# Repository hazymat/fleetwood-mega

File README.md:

# fleetwood-mega
Eagle files for Version 2 of Fleetwood hardware.

Hi reader! The PCB in this project is not ready for production. Parts have not been finalised, traces not yet routed. It's a work in progress.

Latest YouTube project update here: https://www.youtube.com/watch?v=HE-3FGcSKfI
YouTube channel generally full of my MQTT ramblings here: https://www.youtube.com/user/hazymat

Do take a look at the photo of Fleetwood's first prototype installed in the home, included in the repo.

- This project is not ready for production
- The board is based on Freetronics EtherMegaR3 (https://github.com/freetronics/EtherMega)
- Spec as per EtherMega with following changes
 - **Inclusion of 7 LED tactile switches, a click rotary encoder, and OLED display, for controlling home automation hub by MQTT**
 - Change form factor to better fit a double wall socket back box - dry lining box and metal back box
 - Removal of SD card to save space
 - Removal of USB to serial to save space (use external FTDI or TFTP upload of sketch to bootloader)
 - Built-in support for either DIY PoE or 802.3af PoE - as per original EtherMega
 - Ethernet jack moved away from side of board to allow more space for cable / plug insertion in wall box

# LICENCE
This work is licensed under the
Creative Commons Attribution-Share Alike License.  
To view a copy of this license, visit

  http://creativecommons.org/licenses/by-sa/3.0/  
  http://creativecommons.org/licenses/by-sa/3.0/legalcode

or send a letter to

  Creative Commons  
  171 Second Street, Suite 300  
  San Francisco  
  California, 94105  
  USA

The "license" folder within this repository also contains copies of the
licences referenced above.

# CREDITS
The EtherMega was designed by Marc Alexander (marc@freetronics.com) and
Jonathan Oxer (jon@freetronics.com) based on previous work by the Arduino
team (www.arduino.cc/playground/Main/People) which includes:

 * Massimo Banzi
 * David Cuartielles
 * Tom Igoe
 * Gianluca Martino
 * David A. Mellis

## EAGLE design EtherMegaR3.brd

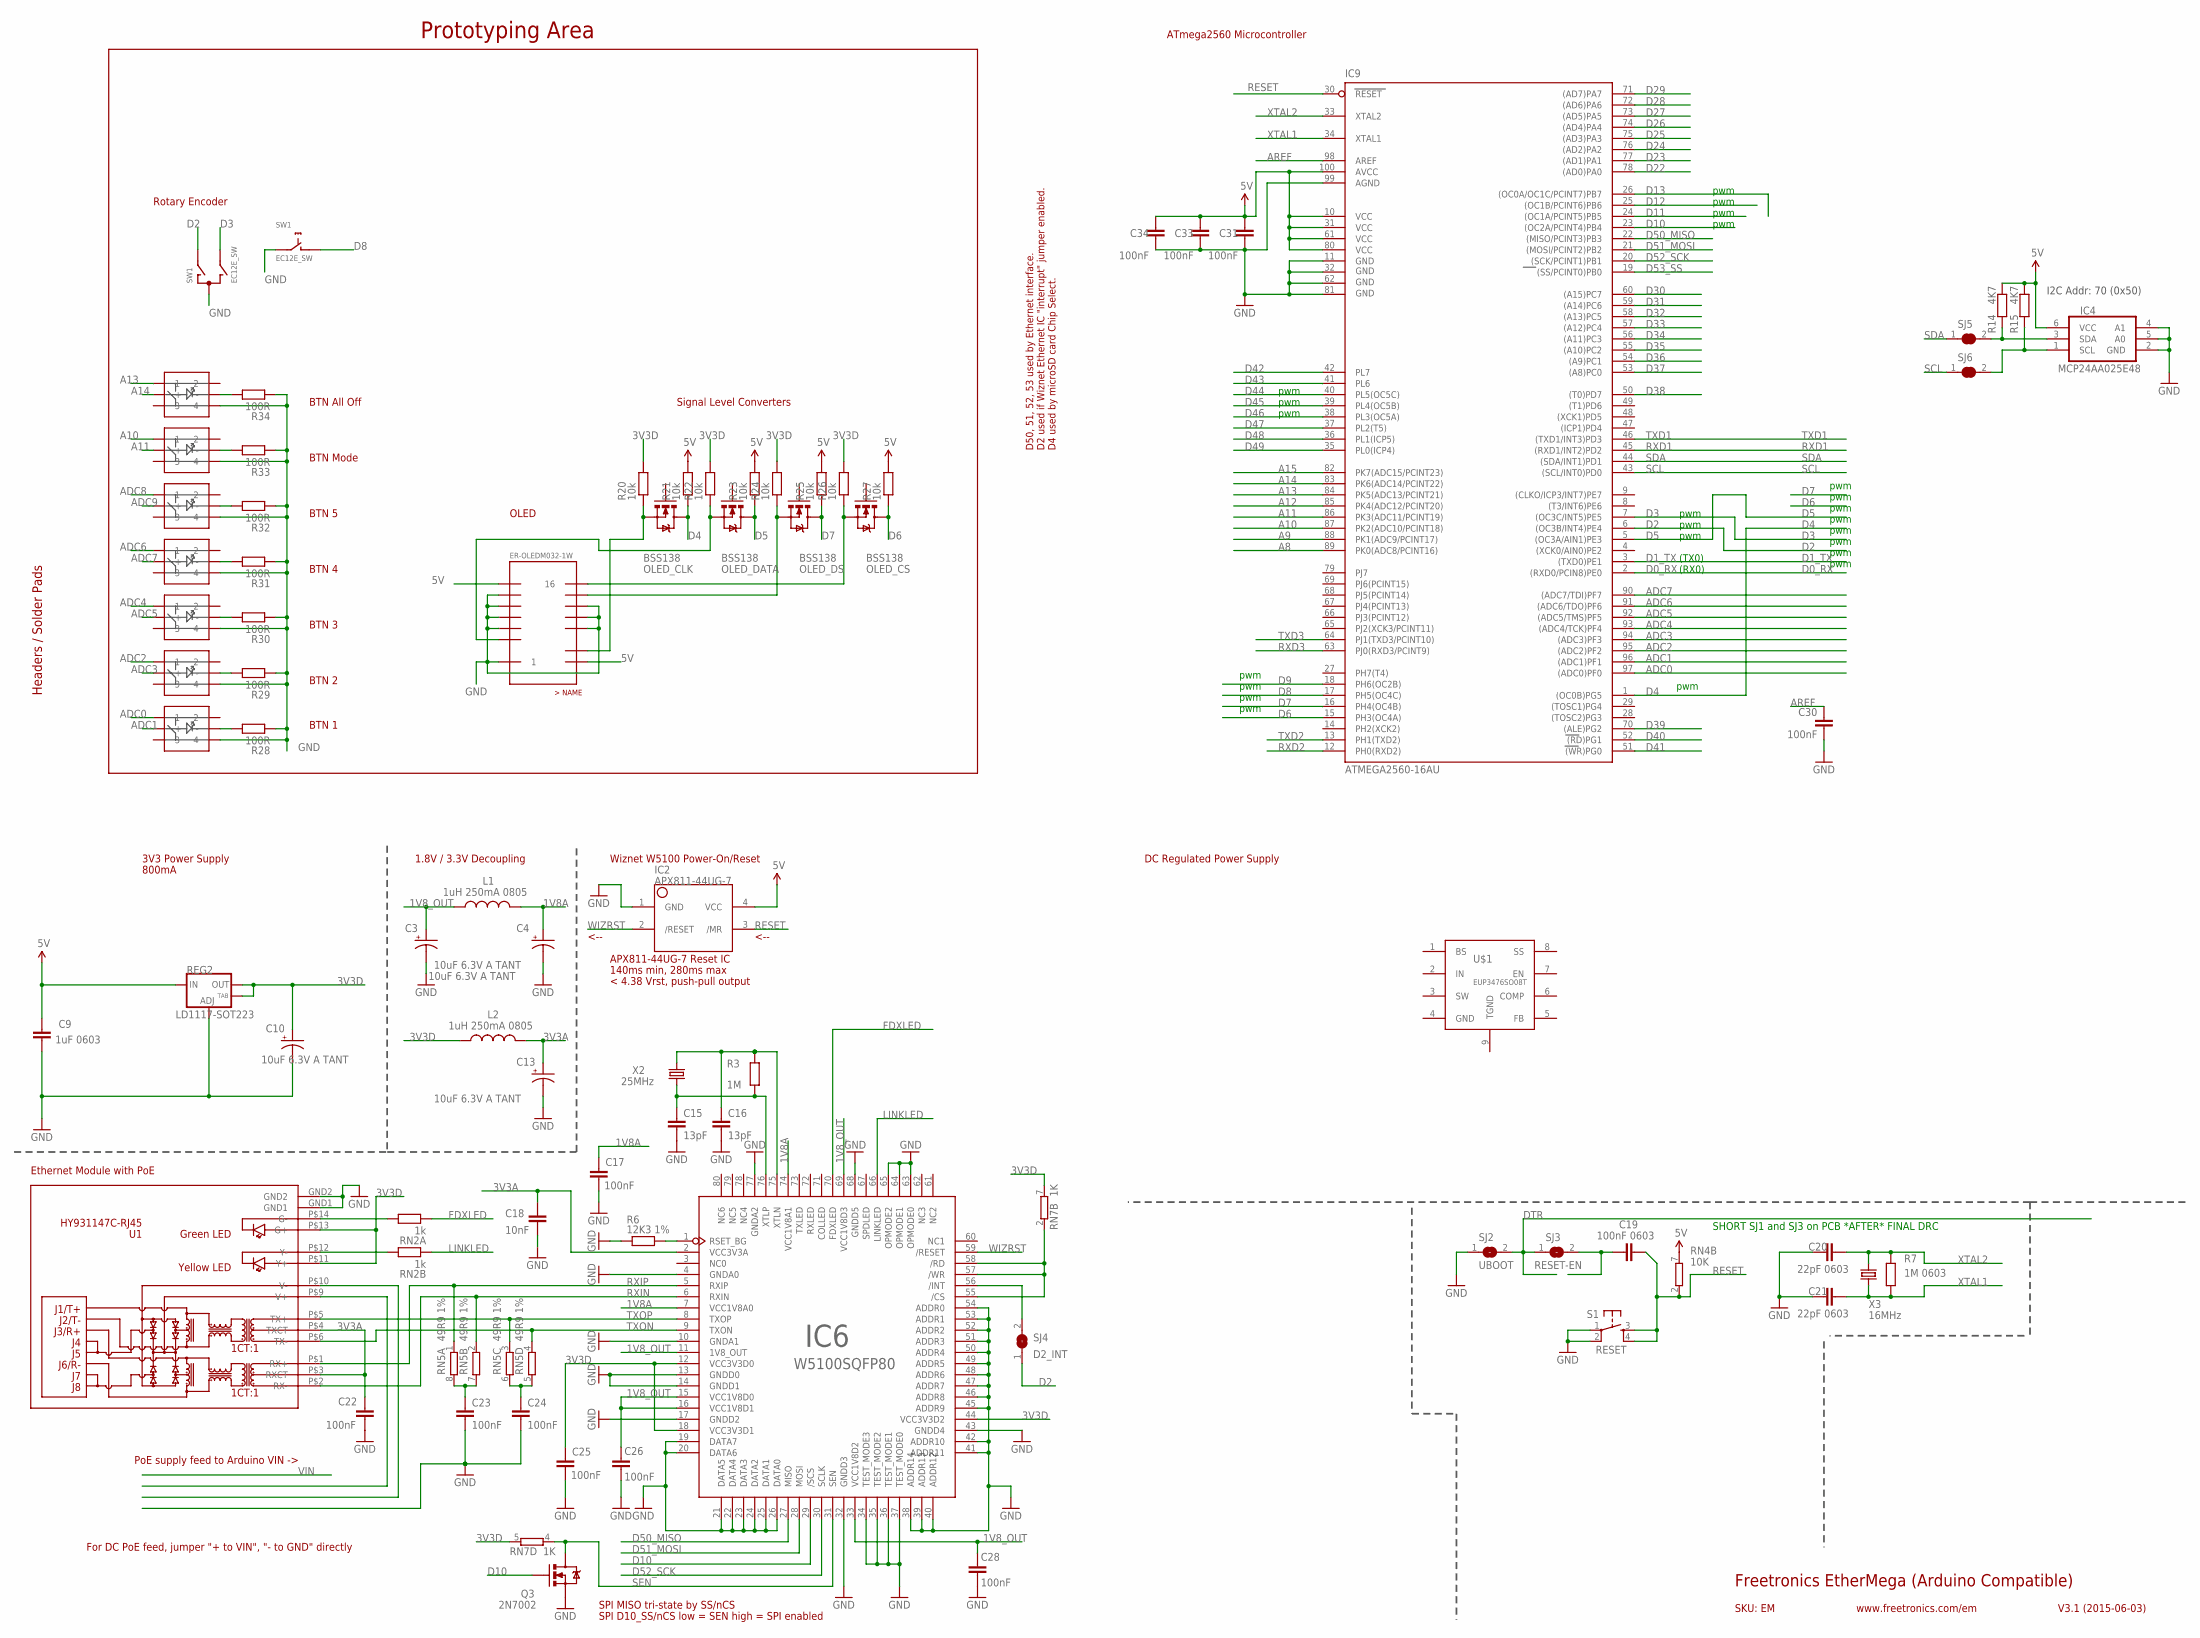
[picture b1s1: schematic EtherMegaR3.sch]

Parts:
BTN_FAVE1, BTN_FAVE2, BTN_FAVE3, BTN_FAVE4, BTN_FAVE5: PB614
BTN_MODE: PB614
BTN_OFF: PB614
C3, C4, C10, C13: 10uF 6.3V A TANT; EIA3216
C9: 1uF 0603; 0603
C15, C16: 13pF; 0603
C17, C22, C23, C24, C25, C26, C28, C30, C31, C33, C34: 100nF; 0603
C18: 10nF; 0603
C19: 100nF 0603; 0603
C20, C21: 22pF 0603; 0603
IC2: APX811-44UG-7; SOT143-R
IC4: MCP24AA025E48; SOT23-6
IC6: W5100SQFP80; SQFP80
IC9: ATMEGA2560-16AU; TQFP100
L1, L2: 1uH 250mA 0805; L2012C
OLED: ER-OLED-M032-1W
OLED_CLK: BSS138; SOT23-3
OLED_CS: BSS138; SOT23-3
OLED_DATA: BSS138; SOT23-3
OLED_DS: BSS138; SOT23-3
Q3: 2N7002; SOT23-3
R3: 1M; 0603
R6: 12K3 1%; 0603
R7: 1M 0603; 0603
R14, R15: 4K7; 0603
R20, R21, R22, R23, R24, R25, R26, R27: 10k; 0603
R28, R29, R30, R31, R32, R33, R34: 100R; 0603
REG2: LD1117-SOT223; SOT223
RN2A, RN2B: 1k; 0603
RN4: 10K; CAY16
RN5: 49R9 1%; CAY16
RN7: 1K; CAY16
S1: RESET; TACTILE_SWITCH_SMD
SJ2: UBOOT; SJ
SJ3: RESET-EN; SJ
SJ4: D2_INT; SJ
SJ5, SJ6: SJCN; SJC
SW1: EC12E_SW; ALPS_EC12E_SW
U1: HY931147C-RJ45; HY931147C
U$1: EUP3476SO08T; SO08T
X2: 25MHz; HC49U-V
X3: 16MHz; HC49U-V

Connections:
1V8A: C4.A (+), C17.1, IC6.7 (VCC1V8A0), IC6.74 (VCC1V8A1), L1.2
1V8_OUT: C3.A (+), C26.1, C28.1, IC6.11 (1V8_OUT), IC6.15 (VCC1V8D0), IC6.16 (VCC1V8D1), IC6.33 (VCC1V8D2), IC6.69 (VCC1V8D3), L1.1
3V3A: C13.A (+), C18.1, C22.1, IC6.2 (VCC3V3A), L2.2, U1.P$3 (RXCT), U1.P$4 (TXCT)
3V3D: C10.A (+), C25.1, IC6.12 (VCC3V3D0), IC6.18 (VCC3V3D1), IC6.44 (VCC3V3D2), L2.1, R20.2, R22.2, R24.2, R26.2, REG2.2 (OUT), REG2.4 (OUT), RN7.5 (2), RN7.7 (2), U1.P$11 (Y+), U1.P$13 (G+)
5V: C9.1, C31.1, C33.1, C34.1, IC2.4 (VCC), IC4.6 (VCC), IC9.10 (VCC), IC9.31 (VCC1), IC9.61 (VCC2), IC9.80 (VCC3), IC9.100 (AVCC), OLED.2, OLED.15, R14.1, R15.1, R21.2, R23.2, R25.2, R27.2, REG2.3 (IN), RN4.7 (2)
A8: IC9.89 (PK0(ADC8/PCINT16))
A9: IC9.88 (PK1(ADC9/PCINT17))
A10: BTN_MODE.1, IC9.87 (PK2(ADC10/PCINT18))
A11: BTN_MODE.L+ (+), IC9.86 (PK3(ADC11/PCINT19))
A12: IC9.85 (PK4(ADC12/PCINT20))
A13: BTN_OFF.1, IC9.84 (PK5(ADC13/PCINT21))
A14: BTN_OFF.L+ (+), IC9.83 (PK6(ADC14/PCINT22))
A15: IC9.82 (PK7(ADC15/PCINT23))
ADC0: BTN_FAVE1.1, IC9.97 ((ADC0)PF0)
ADC1: BTN_FAVE1.L+ (+), IC9.96 ((ADC1)PF1)
ADC2: BTN_FAVE2.1, IC9.95 ((ADC2)PF2)
ADC3: BTN_FAVE2.L+ (+), IC9.94 ((ADC3)PF3)
ADC4: BTN_FAVE3.1, IC9.93 ((ADC4/TCK)PF4)
ADC5: BTN_FAVE3.L+ (+), IC9.92 ((ADC5/TMS)PF5)
ADC6: BTN_FAVE4.1, IC9.91 ((ADC6/TDO)PF6)
ADC7: BTN_FAVE4.L+ (+), IC9.90 ((ADC7/TDI)PF7)
ADC8: BTN_FAVE5.1
ADC9: BTN_FAVE5.L+ (+)
AREF: C30.1, IC9.98 (AREF)
D0_RX: IC9.2 ((RXD0/PCIN8)PE0)
D1_TX: IC9.3 ((TXD0)PE1)
D2: IC9.6 ((OC3B/INT4)PE4), SJ4.1, SW1.A
D3: IC9.7 ((OC3C/INT5)PE5), SW1.B
D4: IC9.1 ((OC0B)PG5), OLED_CLK.3 (D), R21.1
D5: IC9.5 ((OC3A/AIN1)PE3), OLED_DATA.3 (D), R23.1
D6: IC9.15 (PH3(OC4A)), OLED_CS.3 (D), R27.1
D7: IC9.16 (PH4(OC4B)), OLED_DS.3 (D), R25.1
D8: IC9.17 (PH5(OC4C)), SW1.D (1)
D9: IC9.18 (PH6(OC2B))
D10: IC6.29 (/SCS), IC9.23 ((OC2A/PCINT4)PB4), Q3.1 (G)
D11: IC9.24 ((OC1A/PCINT5)PB5)
D12: IC9.25 ((OC1B/PCINT6)PB6)
D13: IC9.26 ((OC0A/OC1C/PCINT7)PB7)
D22: IC9.78 ((AD0)PA0)
D23: IC9.77 ((AD1)PA1)
D24: IC9.76 ((AD2)PA2)
D25: IC9.75 ((AD3)PA3)
D26: IC9.74 ((AD4)PA4)
D27: IC9.73 ((AD5)PA5)
D28: IC9.72 ((AD6)PA6)
D29: IC9.71 ((AD7)PA7)
D30: IC9.60 ((A15)PC7)
D31: IC9.59 ((A14)PC6)
D32: IC9.58 ((A13)PC5)
D33: IC9.57 ((A12)PC4)
D34: IC9.56 ((A11)PC3)
D35: IC9.55 ((A10)PC2)
D36: IC9.54 ((A9)PC1)
D37: IC9.53 ((A8)PC0)
D38: IC9.50 ((T0)PD7)
D39: IC9.70 ((ALE)PG2)
D40: IC9.52 ((RD)PG1)
D41: IC9.51 ((WR)PG0)
D42: IC9.42 (PL7)
D43: IC9.41 (PL6)
D44: IC9.40 (PL5(OC5C))
D45: IC9.39 (PL4(OC5B))
D46: IC9.38 (PL3(OC5A))
D47: IC9.37 (PL2(T5))
D48: IC9.36 (PL1(ICP5))
D49: IC9.35 (PL0(ICP4))
D50_MISO: IC6.27 (MISO), IC9.22 ((MISO/PCINT3)PB3)
D51_MOSI: IC6.28 (MOSI), IC9.21 ((MOSI/PCINT2)PB2)
D52_SCK: IC6.30 (SCLK), IC9.20 ((SCK/PCINT1)PB1)
D53_SS: IC9.19 ((SS/PCINT0)PB0)
DTR: SJ2.2, SJ3.1
FDXLED: IC6.70 (FDXLED), RN2A.1
GND: BTN_FAVE1.4, BTN_FAVE2.4, BTN_FAVE3.4, BTN_FAVE4.4, BTN_FAVE5.4, BTN_MODE.4, BTN_OFF.4, C3.C (-), C4.C (-), C9.2, C10.C (-), C13.C (-), C15.2, C16.2, C17.2, C18.2, C20.1, C21.1, C22.2, C23.2, C24.2, C25.2, C26.2, C28.2, C30.2, C31.2, C33.2, C34.2, IC2.1 (GND), IC4.2 (GND), IC4.4 (A1), IC4.5 (A0), IC6.4 (GNDA0), IC6.10 (GNDA1), IC6.13 (GNDD0), IC6.14 (GNDD1), IC6.17 (GNDD2), IC6.19 (DATA7), IC6.20 (DATA6), IC6.21 (DATA5), IC6.22 (DATA4), IC6.23 (DATA3), IC6.24 (DATA2), IC6.25 (DATA1), IC6.26 (DATA0), IC6.32 (GNDD3), IC6.34 (TEST_MODE3), IC6.35 (TEST_MODE2), IC6.36 (TEST_MODE1), IC6.37 (TEST_MODE0), IC6.38 (ADDR14), IC6.39 (ADDR13), IC6.40 (ADDR12), IC6.41 (ADDR11), IC6.42 (ADDR10), IC6.43 (GNDD4), IC6.45 (ADDR9), IC6.46 (ADDR8), IC6.47 (ADDR7), IC6.48 (ADDR6), IC6.49 (ADDR5), IC6.50 (ADDR4), IC6.51 (ADDR3), IC6.52 (ADDR2), IC6.53 (ADDR1), IC6.54 (ADDR0), IC6.63 (OPMODE0), IC6.64 (OPMODE1), IC6.65 (OPMODE2), IC6.68 (GNDD5), IC6.77 (GNDA2), IC9.11 (GND), IC9.32 (GND1), IC9.62 (GND2), IC9.81 (GND3), IC9.99 (AGND), OLED.1, OLED.7, OLED.8, OLED.9, OLED.10, OLED.11, OLED.12, OLED.13, Q3.2 (S), R6.1, R28.1, R29.1, R30.1, R31.1, R32.1, R33.1, R34.1, REG2.1 (ADJ), S1.1, S1.2, SJ2.1, SW1.C, SW1.E (2), U1.GND1, U1.GND2, U$1.4 (GND)
IN: U$1.2 (IN)
LINKLED: IC6.66 (LINKLED), RN2B.1
unnamed: C24.1, RN5.5 (2), RN5.6 (2)
unnamed: BTN_FAVE1.L- (-), R28.2
unnamed: OLED.4, OLED_CLK.2 (S), R20.1
unnamed: OLED.5, OLED_DATA.2 (S), R22.1
unnamed: BTN_FAVE2.L- (-), R29.2
unnamed: OLED.14, OLED_DS.2 (S), R24.1
unnamed: BTN_FAVE3.L- (-), R30.2
unnamed: OLED.16, OLED_CS.2 (S), R26.1
unnamed: IC4.1 (SCL), R15.2, SJ6.2
unnamed: BTN_FAVE4.L- (-), R31.2
unnamed: BTN_FAVE5.L- (-), R32.2
unnamed: BTN_MODE.L- (-), R33.2
unnamed: BTN_OFF.L- (-), R34.2
unnamed: IC4.3 (SDA), R14.2, SJ5.2
unnamed: IC6.55 (/CS), IC6.57 (/WR), IC6.58 (/RD), RN7.2 (1)
unnamed: IC6.56 (/INT), SJ4.2
unnamed: RN2A.2, U1.P$14 (G-)
unnamed: C19.1, SJ3.2
unnamed: C23.1, RN5.7 (2), RN5.8 (2)
unnamed: IC6.1 (RSET_BG), R6.2
unnamed: RN2B.2, U1.P$12 (Y-)
RESET: C19.2, IC2.3 (/MR), IC9.30 (RESET), RN4.2 (1), S1.3, S1.4
RXD1: IC9.45 ((RXD1/INT2)PD2)
RXD2: IC9.12 (PH0(RXD2))
RXD3: IC9.63 (PJ0(RXD3/PCINT9))
RXIN: IC6.6 (RXIN), RN5.2 (1), U1.P$2 (RX-)
RXIP: IC6.5 (RXIP), RN5.1, U1.P$1 (RX+)
SCL: IC9.43 ((SCL/INT0)PD0), SJ6.1
SDA: IC9.44 ((SDA/INT1)PD1), SJ5.1
SEN: IC6.31 (SEN), Q3.3 (D), RN7.4 (1)
TGND: U$1.9 (TGND)
TXD1: IC9.46 ((TXD1/INT3)PD3)
TXD2: IC9.13 (PH1(TXD2))
TXD3: IC9.64 (PJ1(TXD3/PCINT10))
TXON: IC6.9 (TXON), RN5.4 (1), U1.P$6 (TX-)
TXOP: IC6.8 (TXOP), RN5.3 (1), U1.P$5 (TX+)
WIZRST: IC2.2 (/RESET), IC6.59 (/RESET)
XTAL1: C21.2, IC9.34 (XTAL1), R7.1, X3.1
XTAL2: C20.2, IC9.33 (XTAL2), R7.2, X3.2
XTLN: C16.1, IC6.75 (XTLN), R3.2, X2.2
XTLP: C15.1, IC6.76 (XTLP), R3.1, X2.1

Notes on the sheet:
Prototyping Area
3V3 Power Supply
Headers / Solder Pads
1.8V / 3.3V Decoupling
D50, 51, 52, 53 used by Ethernet interface.
D2 used if Wiznet Ethernet IC "interrupt" jumper enabled.
PoE supply feed to Arduino VIN ->
SPI MISO tri-state by SS/nCS
SPI D10_SS/nCS low = SEN high = SPI enabled
For DC PoE feed, jumper "+ to VIN", "- to GND" directly
DC Regulated Power Supply
ATmega2560 Microcontroller
APX811-44UG-7 Reset IC
140ms min, 280ms max
Wiznet W5100 Power-On/Reset
800mA
Freetronics EtherMega (Arduino Compatible)
V3.1 (2015-06-03)
www.freetronics.com/em
SKU: EM
Ethernet Module with PoE
< 4.38 Vrst, push-pull output
<--
D4 used by microSD card Chip Select.
pwm
(TX0)
(RX0)
SHORT SJ1 and SJ3 on PCB *AFTER* FINAL DRC
I2C Addr: 70 (0x50)
Rotary Encoder
BTN All Off
BTN Mode
BTN 5
BTN 4
BTN 3
BTN 2
BTN 1
Signal Level Converters
OLED

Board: 2 copper layers, 78 parts (33 on the bottom side), 67 nets, no tracks yet.

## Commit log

2015-10-30 add prototype photo
2015-11-02 Updated board outline
2015-11-02 remove eagle.epf
2015-11-02 remove epf
2015-11-03 - Finished placing physical dimensions (button holes, faceplate outlines) - Added Fleetwood components - Added signal level converter (based on Sparkfun bi-directional converter) - Removed REG1 in 3v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
2015-11-04 addition of todo, minor eagle updates
2015-11-04 minor eagle updates
2015-11-04 changed to reflect decisions on spec, etc.
2015-11-04 Added YouTube link to readme
